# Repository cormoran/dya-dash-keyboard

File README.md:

#  DYA Dash Split Keyboard

## Features

- Controller: XIAO NRF52840
- Firmware: ZMK
- Switch: Kailh Choc v2, hotswappable (2pin)
- AAA battery (1.2V NiMH or 1.5V)
- Touch sensor buttons ([See movie how it works](https://x.com/cormoran707/status/1916127921720463540))
- PMW3610 low power trackball sensor
- LED x 4 x 2 for BLE profile, battery level indication ([See movie how it works](https://youtu.be/y6X2OnoMX-M))
- Hardware capability for below features (Not tested yet)
  - Dual trackball support
  - Wired connection

## Build Guide

- [V2.0 ビルドガイド](./hardware/dya-dash/build-guide/v2/BuildGuide.md)
- [V1.0 (試作) ビルドガイド](./hardware/dya-dash/build-guide/v1/BuildGuide.md)

## Firmware

Firmware is available in https://github.com/cormoran/zmk-keyboard-dya-dash.

You can download pre-built binaries in [the release page](https://github.com/cormoran/zmk-keyboard-dya-dash/releases).

The firmware supports keymapping update with [ZMK studio](https://zmk.studio/).

## Gallery

### Schematic

Left side schematic

### Double trackball supported

### Colors

### Bottom

### LED indicators

4x2 LEDs indicates battery level, connected BLE/USB profiles and active layers depending on the setting.
The schematic and firmware driver is optimized for battery usage. LED modules consume power only when required.

> [!NOTE]
> The picture is old version's one

## Shop

Now on sale in https://cormoran707.booth.pm/

## License

- Firmware (./firmware): MIT. See detail in each git submodule.
- DYA logo  (./img/dya.svg): All rights reserved.
- Other keyboard pictures under ./img: CC BY
- Hardware
  - kicad library (./hardware/kicad_library/\*) and sch (\*.kicad_sch): MIT
  - PCB (\*.kicad_pcb): CC BY-NC
  - Case data (\*.stl): CC BY

完全なコピー品が販売された場合に対応できるように PCB 設計を流用して販売することは禁止していますが、回路設計を真似たり似たような設計のキーボードを作ることを牽制したりする意図はありません。

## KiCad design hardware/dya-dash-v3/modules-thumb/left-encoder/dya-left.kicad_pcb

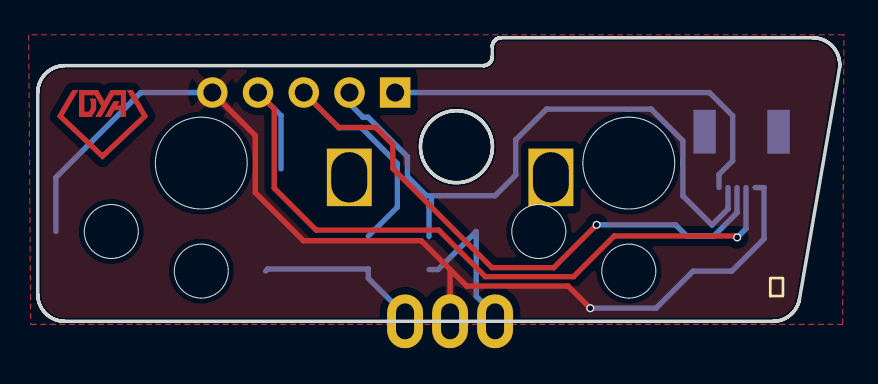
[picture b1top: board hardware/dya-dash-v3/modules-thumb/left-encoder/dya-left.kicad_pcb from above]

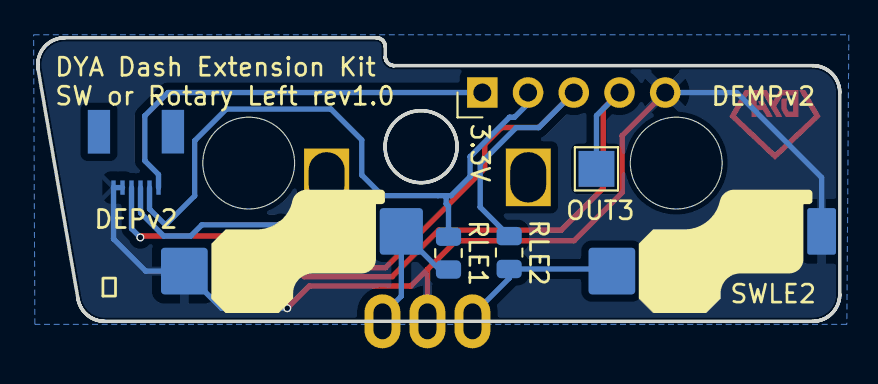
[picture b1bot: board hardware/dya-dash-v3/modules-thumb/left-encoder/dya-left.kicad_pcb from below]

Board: 2 copper layers, 44.6 x 15.8 mm, 8 parts (7 on the bottom side), 7 nets.

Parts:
JLE1: FFC; JUSHUO-AFH34-S06FIA-1H
JLE2: Magnet Connector; PinHeader_1x05_P2.54mm_Vertical
JLE3: Conn_01x01_Socket; TestPoint_Pad_2.0x2.0mm
RLE1, RLE2: 330Ω; R_0805_2012Metric
SWELE1: RotaryEncoder_Switch; RotaryEncoder_EC12E
SWLE1, SWLE2: SW_Push_45deg; Kailh-PG1353-Hotswap-1U

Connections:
3.3V_L: JLE1.1, JLE2.1
ENC1_LE: RLE1.2, SWELE1.B, SWLE1.1
ENC2_LE: RLE2.2, SWELE1.A, SWLE2.2
GNDLE: JLE1.5, JLE1.6, JLE2.5, SWELE1.C, SWLE1.2, SWLE2.1
OUT1: JLE1.2, JLE2.2, RLE1.1
OUT2: JLE1.3, JLE2.3, RLE2.1
OUT3: JLE1.4, JLE2.4, JLE3.1

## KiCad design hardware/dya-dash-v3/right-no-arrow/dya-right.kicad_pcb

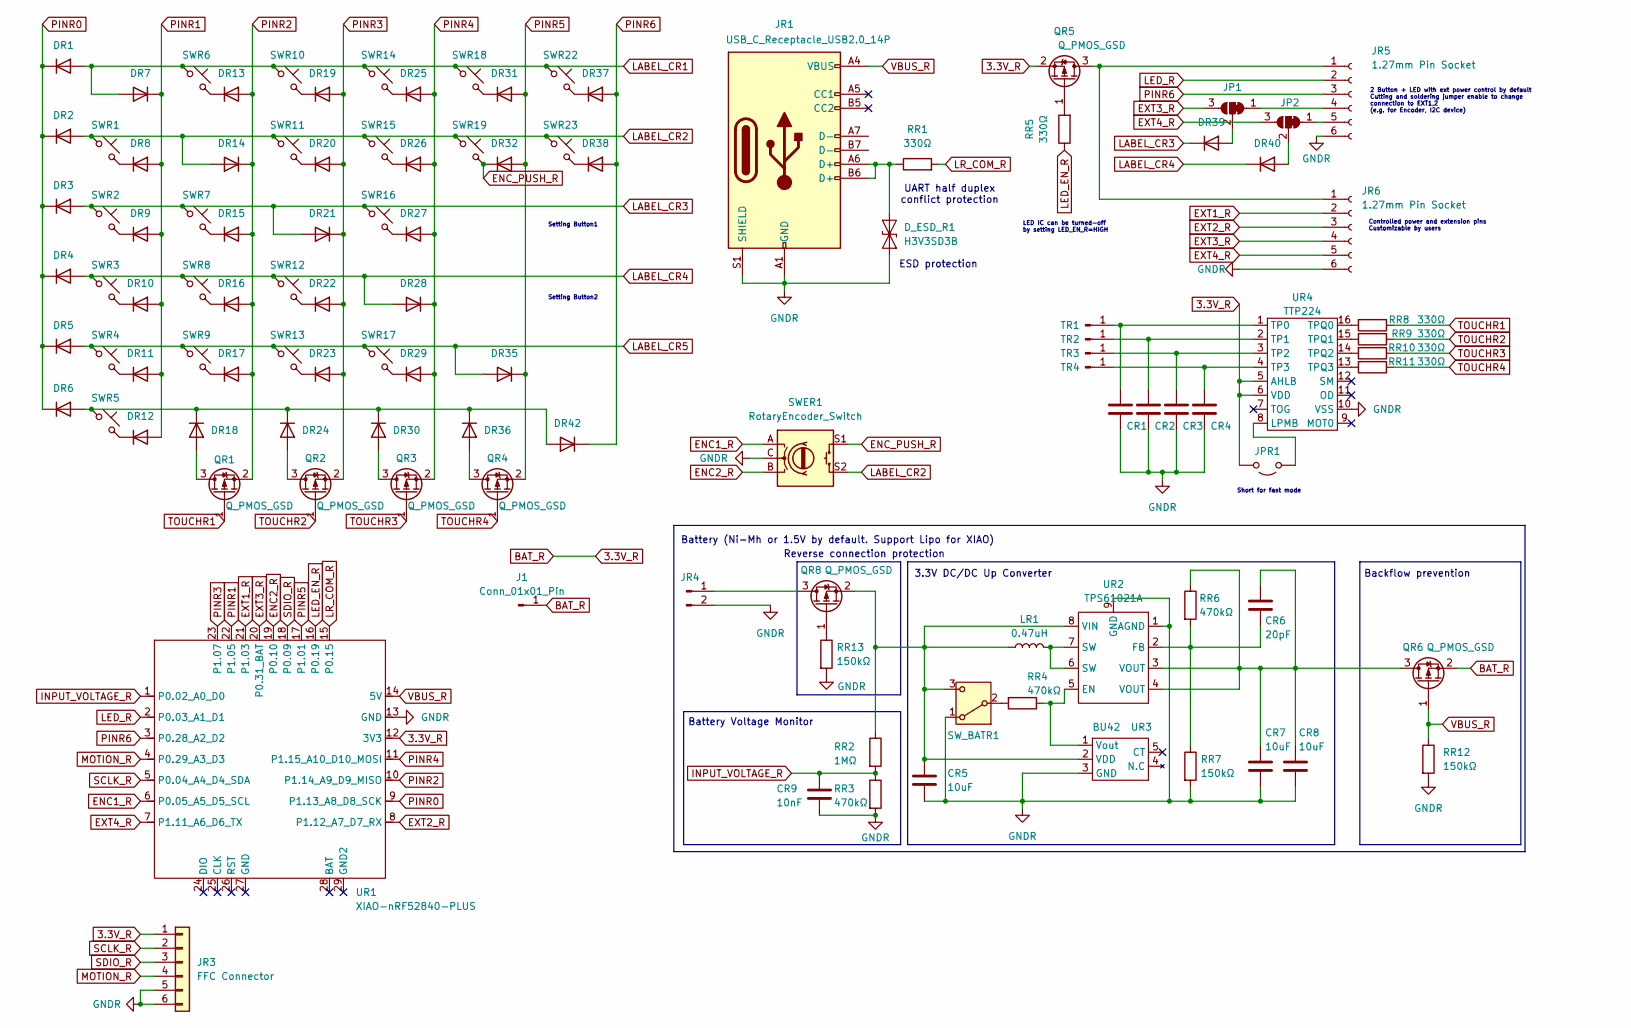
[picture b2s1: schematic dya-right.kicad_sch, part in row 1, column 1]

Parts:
CR1, CR2, CR3, CR4: C_0805_2012Metric
CR5, CR7, CR8: 10uF; C_0805_2012Metric; LCSC C15850
CR6: 20pF; C_0805_2012Metric; LCSC C1798
CR9: 10nF; C_0805_2012Metric
DR1, DR2, DR3, DR4, DR5, DR6, DR7, DR8, DR9, DR10, DR11, DR12, DR13, DR14, DR15, DR16, DR17, DR18, DR19, DR20, DR21, DR22, DR23, DR24, DR25, DR26, DR27, DR28, DR29, DR30, DR31, DR32, DR35, DR36, DR37, DR38, DR39, DR40, DR42: D; D_SOD-123; LCSC C81598
D_ESD_R1: H3V3SD3B; D_SOD-323; LCSC C20615802
J1: Conn_01x01_Pin; TestPoint_Pad_1.5x1.5mm
JP1, JP2: SolderJumper_3_Bridged12; SolderJumper-3_P1.3mm_Bridged12_RoundedPad1.0x1.5mm
JPR1: Jumper_2_Open; SolderJumper-2_P1.3mm_Open_RoundedPad1.0x1.5mm
JR1: USB_C_Receptacle_USB2.0_14P; USB_C_ Recessed_ YTC-TC16-31_1.2mm; LCSC C2927296
JR3: FFC Connector; JUSHUO-AFH34-S06FIA-1H; LCSC C224194
JR4: Conn_01x02_Pin; AAA-battery
JR5, JR6: 1.27mm Pin Socket; PinHeader_1x06_P1.27mm_Vertical
LR1: 0.47uH; L_1008_2520Metric; LCSC C519277
QR1, QR2, QR3, QR4, QR5, QR6: Q_PMOS_GSD; SOT-23; LCSC C15127
QR8: Q_PMOS_GSD; SOT-23; LCSC C144153
RR1, RR5, RR8, RR9, RR10, RR11: 330Ω; R_0805_2012Metric; LCSC C17630
RR2: 1MΩ; R_0805_2012Metric; LCSC C17514
RR3, RR4, RR6: 470kΩ; R_0805_2012Metric; LCSC C17709
RR7, RR12, RR13: 150kΩ; R_0805_2012Metric; LCSC C17470
SWER1: RotaryEncoder_Switch; RotaryEncoder_Alps_EC12E-Switch_Vertical_H20mm
SWR1, SWR2, SWR3, SWR4, SWR5, SWR6, SWR7, SWR8, SWR9, SWR10, SWR11, SWR12, SWR13, SWR14, SWR15, SWR16, SWR17, SWR18, SWR19, SWR22, SWR23: SW_Push_45deg; Kailh-PG1353-Hotswap-1U; LCSC C5333465
SW_BATR1: SW_SPDT; SSSS811101; LCSC C109335
TR1, TR2, TR3, TR4: Conn_01x01_Pin; MountingHole_2.2mm_M2_Pad
UR1: XIAO-nRF52840-PLUS; XIAO_nRF52840_plus
UR2: TPS61021A; WSON-8-1EP_2x2mm_P0.5mm_EP0.9x1.6mm; LCSC C193037
UR3: BU42; BU42XX; LCSC C2066584
UR4: TTP224; SSOP-16_3.9x4.9mm_P0.635mm; LCSC C2890350

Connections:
3.3V_R: J1.1, JPR1.2 (B), JR3.1, QR5.2 (S), QR6.2 (S), UR1.12 (3V3), UR4.5 (AHLB), UR4.6 (VDD)
ENC1_R: SWER1.A, UR1.6 (P0.05_A5_D5_SCL)
ENC2_R: SWER1.B, UR1.19 (P0.10)
ENC_PUSH_R: DR32.1 (K), SWER1.S1, SWR19.2
EXT1_R: JR6.2, UR1.21 (P1.03)
EXT2_R: JR6.3, UR1.8 (P1.12_A7_D7_RX)
EXT3_R: JP1.3 (B), JR6.4, UR1.20 (P0.31_BAT)
EXT4_R: JP2.3 (B), JR6.5, UR1.7 (P1.11_A6_D6_TX)
GNDR: CR1.2, CR2.2, CR3.2, CR4.2, CR5.2, CR7.2, CR8.2, CR9.2, D_ESD_R1.2 (A2), JR1.A1 (GND), JR1.A12 (GND), JR1.B1 (GND), JR1.B12 (GND), JR1.S1 (SHIELD), JR3.5, JR3.6, JR4.2, JR5.6, JR6.6, RR3.2, RR7.2, RR12.2, RR13.2, SWER1.C, SW_BATR1.1 (A), UR1.13 (GND), UR2.1 (AGND), UR2.9 (GND), UR3.3 (GND), UR4.10 (VSS)
INPUT_VOLTAGE_R: CR9.1, RR2.2, RR3.1, UR1.1 (P0.02_A0_D0)
LABEL_CR1: DR1.2 (A), DR7.2 (A), SWR6.1, SWR10.1, SWR14.1, SWR18.1, SWR22.1
LABEL_CR2: DR2.2 (A), DR14.2 (A), SWER1.S2, SWR1.1, SWR11.1, SWR15.1, SWR19.1, SWR23.1
LABEL_CR3: DR3.2 (A), DR21.2 (A), DR39.1 (K), SWR2.1, SWR7.1, SWR16.1
LABEL_CR4: DR4.2 (A), DR28.2 (A), DR40.1 (K), SWR3.1, SWR8.1, SWR12.1
LABEL_CR5: DR5.2 (A), DR35.2 (A), SWR4.1, SWR9.1, SWR13.1, SWR17.1
LED_EN_R: RR5.1, UR1.16 (P0.19)
LED_R: JR5.2, UR1.2 (P0.03_A1_D1)
LR_COM_R: RR1.2, UR1.15 (P0.15)
MOTION_R: JR3.4, UR1.4 (P0.29_A3_D3)
unnamed: DR8.1 (K), SWR1.2
unnamed: DR9.1 (K), SWR2.2
unnamed: DR10.1 (K), SWR3.2
unnamed: DR11.1 (K), SWR4.2
unnamed: DR12.1 (K), SWR5.2
unnamed: DR13.1 (K), SWR6.2
unnamed: DR15.1 (K), SWR7.2
unnamed: DR16.1 (K), SWR8.2
unnamed: DR17.1 (K), SWR9.2
unnamed: DR18.2 (A), QR1.3 (D)
unnamed: DR6.2 (A), DR18.1 (K), DR24.1 (K), DR30.1 (K), DR36.1 (K), DR42.2 (A), SWR5.1
unnamed: DR19.1 (K), SWR10.2
unnamed: DR20.1 (K), SWR11.2
unnamed: DR22.1 (K), SWR12.2
unnamed: DR23.1 (K), SWR13.2
unnamed: DR24.2 (A), QR2.3 (D)
unnamed: DR25.1 (K), SWR14.2
unnamed: DR26.1 (K), SWR15.2
unnamed: DR27.1 (K), SWR16.2
unnamed: DR29.1 (K), SWR17.2
unnamed: DR30.2 (A), QR3.3 (D)
unnamed: DR31.1 (K), SWR18.2
unnamed: DR36.2 (A), QR4.3 (D)
unnamed: DR37.1 (K), SWR22.2
unnamed: DR38.1 (K), SWR23.2
unnamed: DR39.2 (A), JP1.2 (C)
unnamed: DR40.2 (A), JP2.2 (C)
unnamed: D_ESD_R1.1 (A1), JR1.A6 (D+), JR1.B6 (D+), RR1.1
unnamed: JP1.1 (A), JR5.4
unnamed: JP2.1 (A), JR5.5
unnamed: JPR1.1 (A), UR4.8 (LPMB)
unnamed: JR4.1, QR8.3 (D)
unnamed: JR5.1, JR6.1, QR5.3 (D)
unnamed: LR1.2, UR2.6 (SW), UR2.7 (SW)
unnamed: QR5.1 (G), RR5.2
unnamed: CR6.1, CR7.1, CR8.1, QR6.3 (D), RR6.1, UR2.3 (VOUT), UR2.4 (VOUT)
unnamed: QR8.1 (G), RR13.1
unnamed: CR5.1, LR1.1, QR8.2 (S), RR2.1, SW_BATR1.3 (C), UR2.8 (VIN), UR3.2 (VDD)
unnamed: RR4.2, SW_BATR1.2 (B)
unnamed: CR1.1, TR1.1, UR4.1 (TP0)
unnamed: CR2.1, TR2.1, UR4.2 (TP1)
unnamed: CR3.1, TR3.1, UR4.3 (TP2)
unnamed: CR4.1, TR4.1, UR4.4 (TP3)
unnamed: RR4.1, UR2.5 (EN), UR3.1 (Vout)
unnamed: CR6.2, RR6.2, RR7.1, UR2.2 (FB)
unnamed: RR8.2, UR4.16 (TPQ0)
unnamed: RR9.2, UR4.15 (TPQ1)
unnamed: RR10.2, UR4.14 (TPQ2)
unnamed: RR11.2, UR4.13 (TPQ3)
PINR0: DR1.1 (K), DR2.1 (K), DR3.1 (K), DR4.1 (K), DR5.1 (K), DR6.1 (K), UR1.9 (P1.13_A8_D8_SCK)
PINR1: DR7.1 (K), DR8.2 (A), DR9.2 (A), DR10.2 (A), DR11.2 (A), DR12.2 (A), UR1.22 (P1.05)
PINR2: DR13.2 (A), DR14.1 (K), DR15.2 (A), DR16.2 (A), DR17.2 (A), QR1.2 (S), UR1.10 (P1.14_A9_D9_MISO)
PINR3: DR19.2 (A), DR20.2 (A), DR21.1 (K), DR22.2 (A), DR23.2 (A), QR2.2 (S), UR1.23 (P1.07)
PINR4: DR25.2 (A), DR26.2 (A), DR27.2 (A), DR28.1 (K), DR29.2 (A), QR3.2 (S), UR1.11 (P1.15_A10_D10_MOSI)
PINR5: DR31.2 (A), DR32.2 (A), DR35.1 (K), QR4.2 (S), UR1.17 (P1.01)
PINR6: DR37.2 (A), DR38.2 (A), DR42.1 (K), JR5.3, UR1.3 (P0.28_A2_D2)
SCLK_R: JR3.2, UR1.5 (P0.04_A4_D4_SDA)
SDIO_R: JR3.3, UR1.18 (P0.09)
TOUCHR1: QR1.1 (G), RR8.1
TOUCHR2: QR2.1 (G), RR9.1
TOUCHR3: QR3.1 (G), RR10.1
TOUCHR4: QR4.1 (G), RR11.1
VBUS_R: JR1.A4 (VBUS), JR1.A9 (VBUS), JR1.B4 (VBUS), JR1.B9 (VBUS), QR6.1 (G), RR12.1, UR1.14 (5V)

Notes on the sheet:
Battery (Ni-Mh or 1.5V by default. Support Lipo for XIAO)
2 Button + LED with ext power control by default Cutting and soldering jumper enable to change connection to EXT1,2 (e.g. for Encoder, I2C device)
Short for fast mode
Setting Button1
3.3V DC/DC Up Converter
ESD protection
UART half duplex conflict protection
Backflow prevention
Reverse connection protection
LED IC can be turned-off by setting LED_EN_R=HIGH
Battery Voltage Monitor
Setting Button2
Controlled power and extension pins Customizable by users

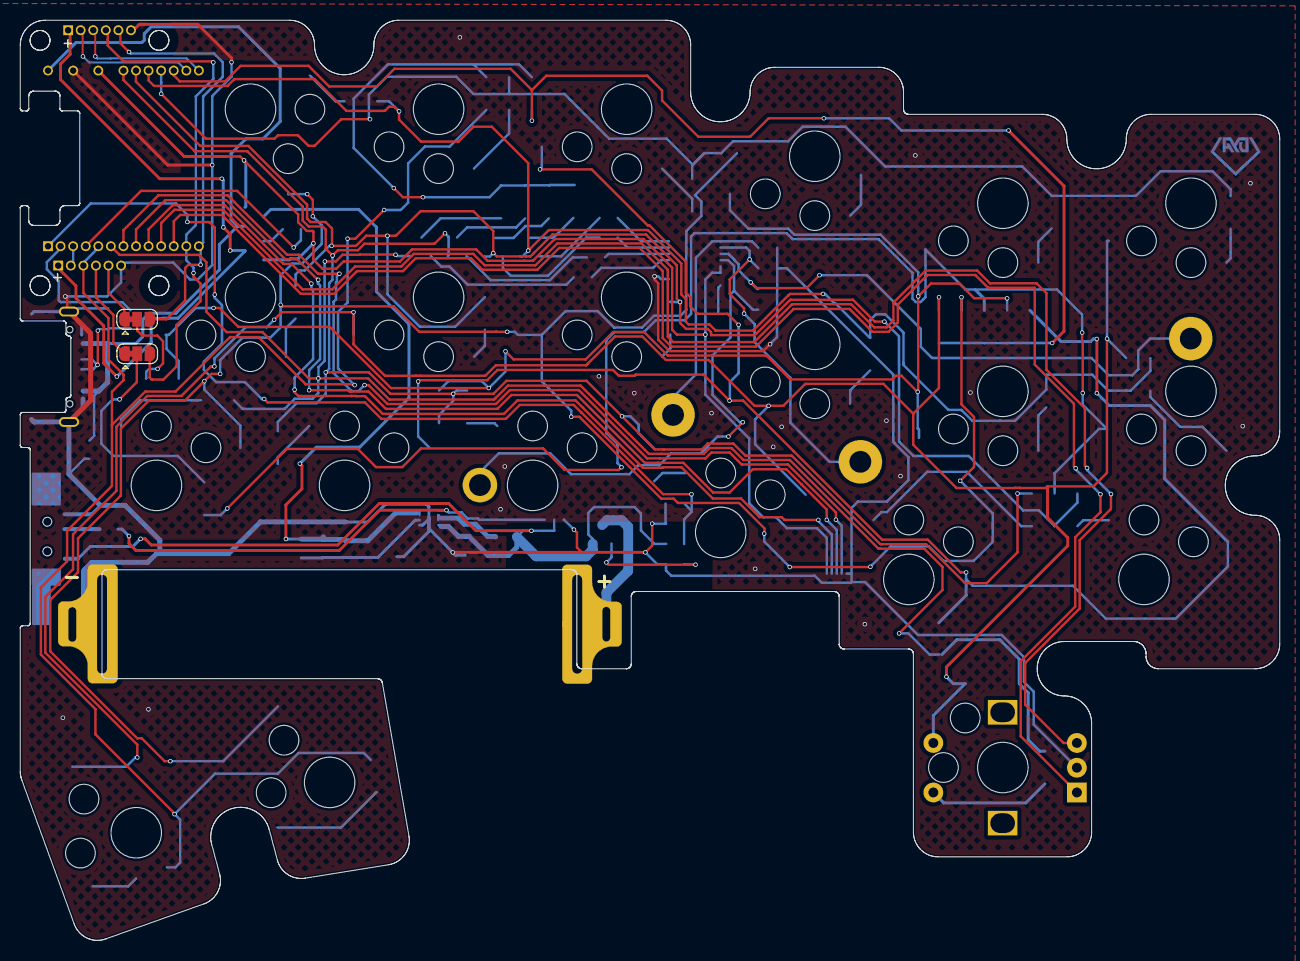
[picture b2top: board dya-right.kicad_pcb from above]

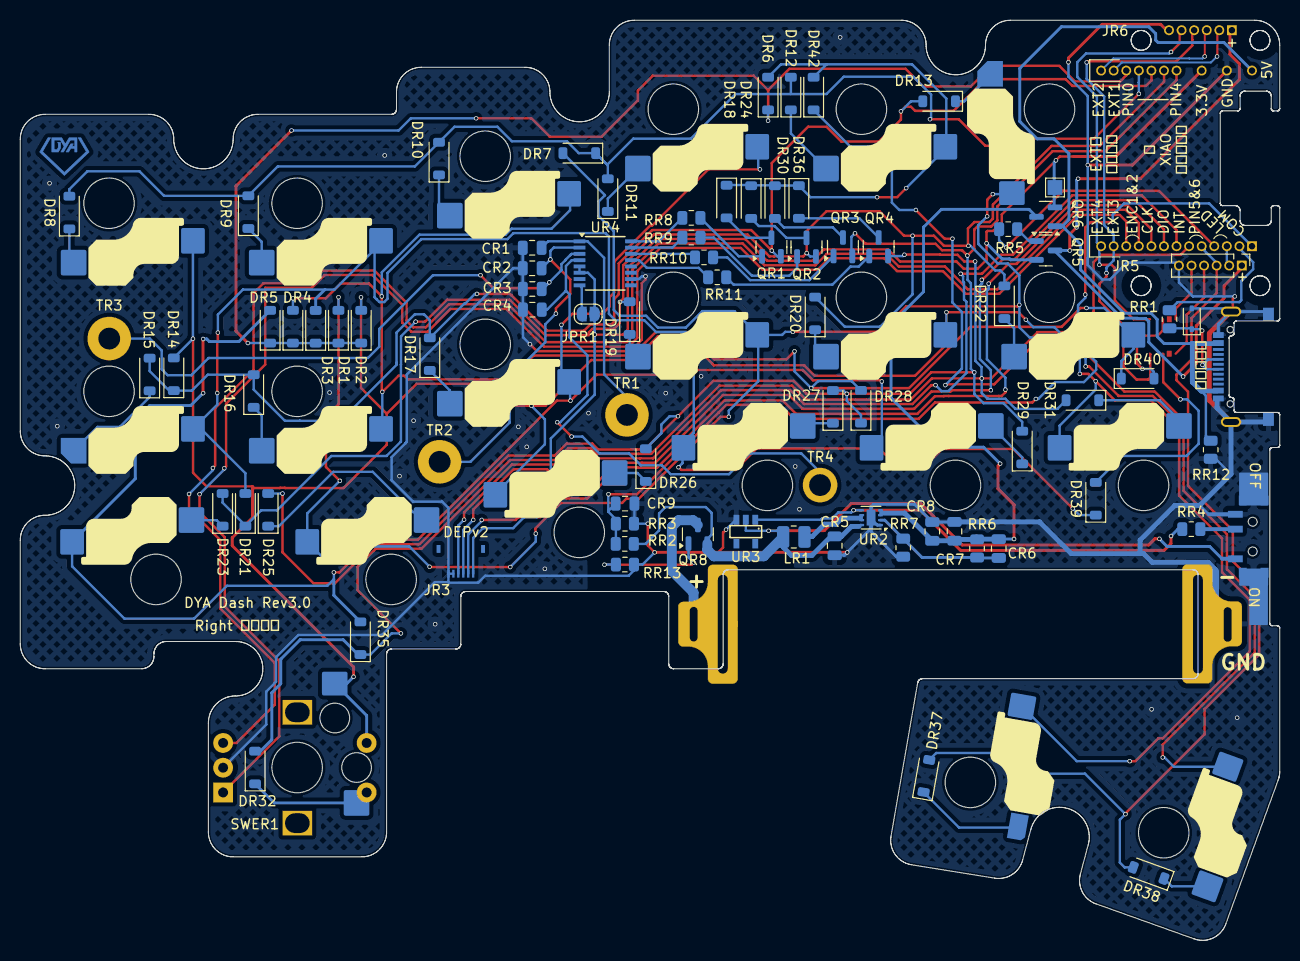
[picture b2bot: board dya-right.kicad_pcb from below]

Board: 2 copper layers, 127.2 x 92.9 mm, 110 parts (104 on the bottom side), 82 nets.

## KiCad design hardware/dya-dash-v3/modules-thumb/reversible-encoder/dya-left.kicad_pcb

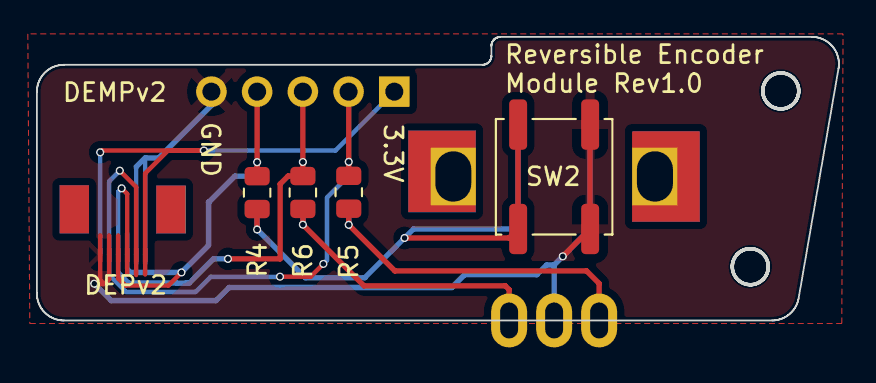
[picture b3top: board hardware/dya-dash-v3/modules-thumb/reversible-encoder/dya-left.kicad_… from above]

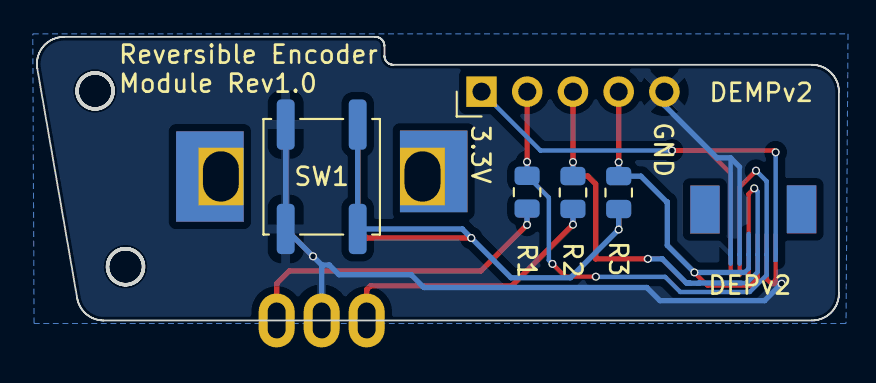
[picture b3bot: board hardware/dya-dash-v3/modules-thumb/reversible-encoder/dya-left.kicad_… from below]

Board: 2 copper layers, 44.6 x 15.8 mm, 12 parts (6 on the bottom side), 8 nets.

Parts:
J1, J3: FFC; JUSHUO-AFH34-S06FIA-1H
J2: Magnet Connector; PinHeader_1x05_P2.54mm_Vertical
R1, R2, R3, R4, R5, R6: 330Ω; R_0805_2012Metric
SW1, SW2: SW_Push_45deg; SW_Push_1P1T_NO_CK_KSC6xxJ
SWE1: RotaryEncoder_Switch; RotaryEncoder_EC12E

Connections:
3.3V_L: J1.1, J2.1, J3.1
ENC1_LE: R1.2, R5.2, SWE1.B
ENC2_LE: R2.2, R6.2, SWE1.A
GNDLE: J1.5, J1.6, J2.5, J3.5, J3.6, SW1.2, SW2.1, SWE1.C
unnamed: R3.1, R4.1, SW1.1, SW2.2
OUT1: J1.2, J2.2, J3.2, R1.1, R5.1
OUT2: J1.3, J2.3, J3.3, R2.1, R6.1
OUT3: J1.4, J2.4, J3.4, R3.2, R4.2

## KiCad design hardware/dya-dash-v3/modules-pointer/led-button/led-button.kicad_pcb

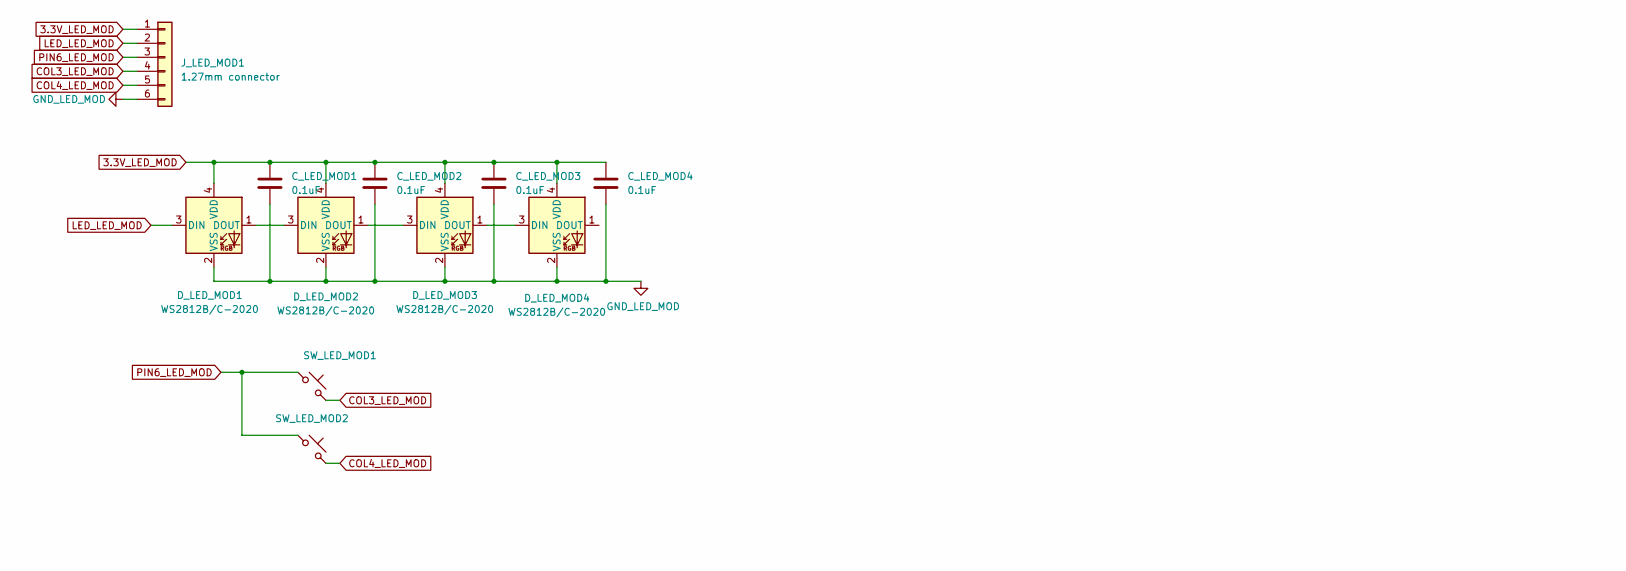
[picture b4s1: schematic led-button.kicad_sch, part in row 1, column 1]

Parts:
C_LED_MOD1, C_LED_MOD2, C_LED_MOD3, C_LED_MOD4: 0.1uF; C_0402_1005Metric; LCSC C1525
D_LED_MOD1, D_LED_MOD2, D_LED_MOD3, D_LED_MOD4: WS2812B/C-2020; LED_WS2812B-2020_PLCC4_2.0x2.0mm; LCSC C2976072
J_LED_MOD1: 1.27mm connector; PinHeader_1x06_P1.27mm_Vertical
SW_LED_MOD1, SW_LED_MOD2: SW_Push; SW_PUSH_1P1T_6x3.5mm_H4.3_APEM_MJTP1243

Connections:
3.3V_LED_MOD: C_LED_MOD1.1, C_LED_MOD2.1, C_LED_MOD3.1, C_LED_MOD4.1, D_LED_MOD1.4 (VDD), D_LED_MOD2.4 (VDD), D_LED_MOD3.4 (VDD), D_LED_MOD4.4 (VDD), J_LED_MOD1.1
COL3_LED_MOD: J_LED_MOD1.4, SW_LED_MOD1.2
COL4_LED_MOD: J_LED_MOD1.5, SW_LED_MOD2.2
GND_LED_MOD: C_LED_MOD1.2, C_LED_MOD2.2, C_LED_MOD3.2, C_LED_MOD4.2, D_LED_MOD1.2 (VSS), D_LED_MOD2.2 (VSS), D_LED_MOD3.2 (VSS), D_LED_MOD4.2 (VSS), J_LED_MOD1.6
LED_LED_MOD: D_LED_MOD1.3 (DIN), J_LED_MOD1.2
unnamed: D_LED_MOD1.1 (DOUT), D_LED_MOD2.3 (DIN)
unnamed: D_LED_MOD2.1 (DOUT), D_LED_MOD3.3 (DIN)
unnamed: D_LED_MOD3.1 (DOUT), D_LED_MOD4.3 (DIN)
PIN6_LED_MOD: J_LED_MOD1.3, SW_LED_MOD1.1, SW_LED_MOD2.1

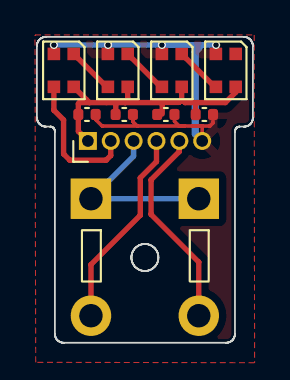
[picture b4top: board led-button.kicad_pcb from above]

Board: 2 copper layers, 12.0 x 17.0 mm, 11 parts (0 on the bottom side), 9 nets.

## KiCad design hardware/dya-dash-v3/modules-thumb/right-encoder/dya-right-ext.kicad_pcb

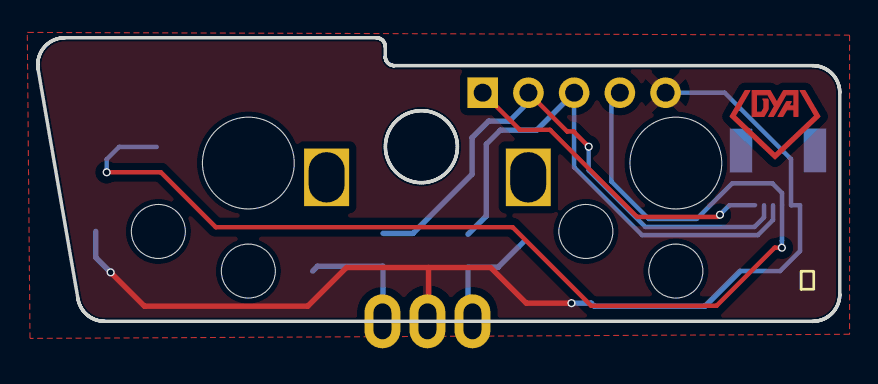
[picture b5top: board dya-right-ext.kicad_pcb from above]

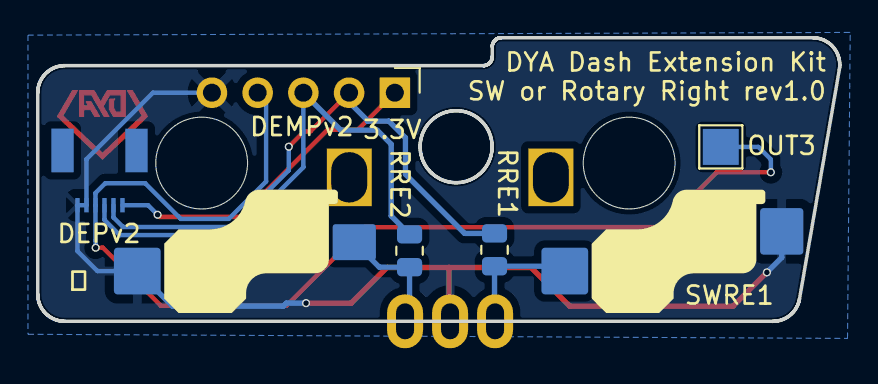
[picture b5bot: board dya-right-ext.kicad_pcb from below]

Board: 2 copper layers, 44.6 x 15.8 mm, 8 parts (7 on the bottom side), 7 nets.

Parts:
JRE1: FFC; JUSHUO-AFH34-S06FIA-1H
JRE2: Magnet Connector; PinHeader_1x05_P2.54mm_Vertical
JRE3: Conn_01x01_Socket; TestPoint_Pad_2.0x2.0mm
RRE1, RRE2: 330Ω; R_0805_2012Metric
SWERE1: RotaryEncoder_Switch; RotaryEncoder_EC12E
SWRE1, SWRE2: SW_Push_45deg; Kailh-PG1353-Hotswap-1U

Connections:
3.3V_RE: JRE1.1, JRE2.1
ENC1_RE: RRE1.2, SWERE1.A, SWRE1.2
ENC2_RE: RRE2.2, SWERE1.B, SWRE2.1
GNDRE: JRE1.5, JRE1.6, JRE2.5, SWERE1.C, SWRE1.1, SWRE2.2
OUT_RE1: JRE1.2, JRE2.2, RRE1.1
OUT_RE2: JRE1.3, JRE2.3, RRE2.1
OUT_RE3: JRE1.4, JRE2.4, JRE3.1

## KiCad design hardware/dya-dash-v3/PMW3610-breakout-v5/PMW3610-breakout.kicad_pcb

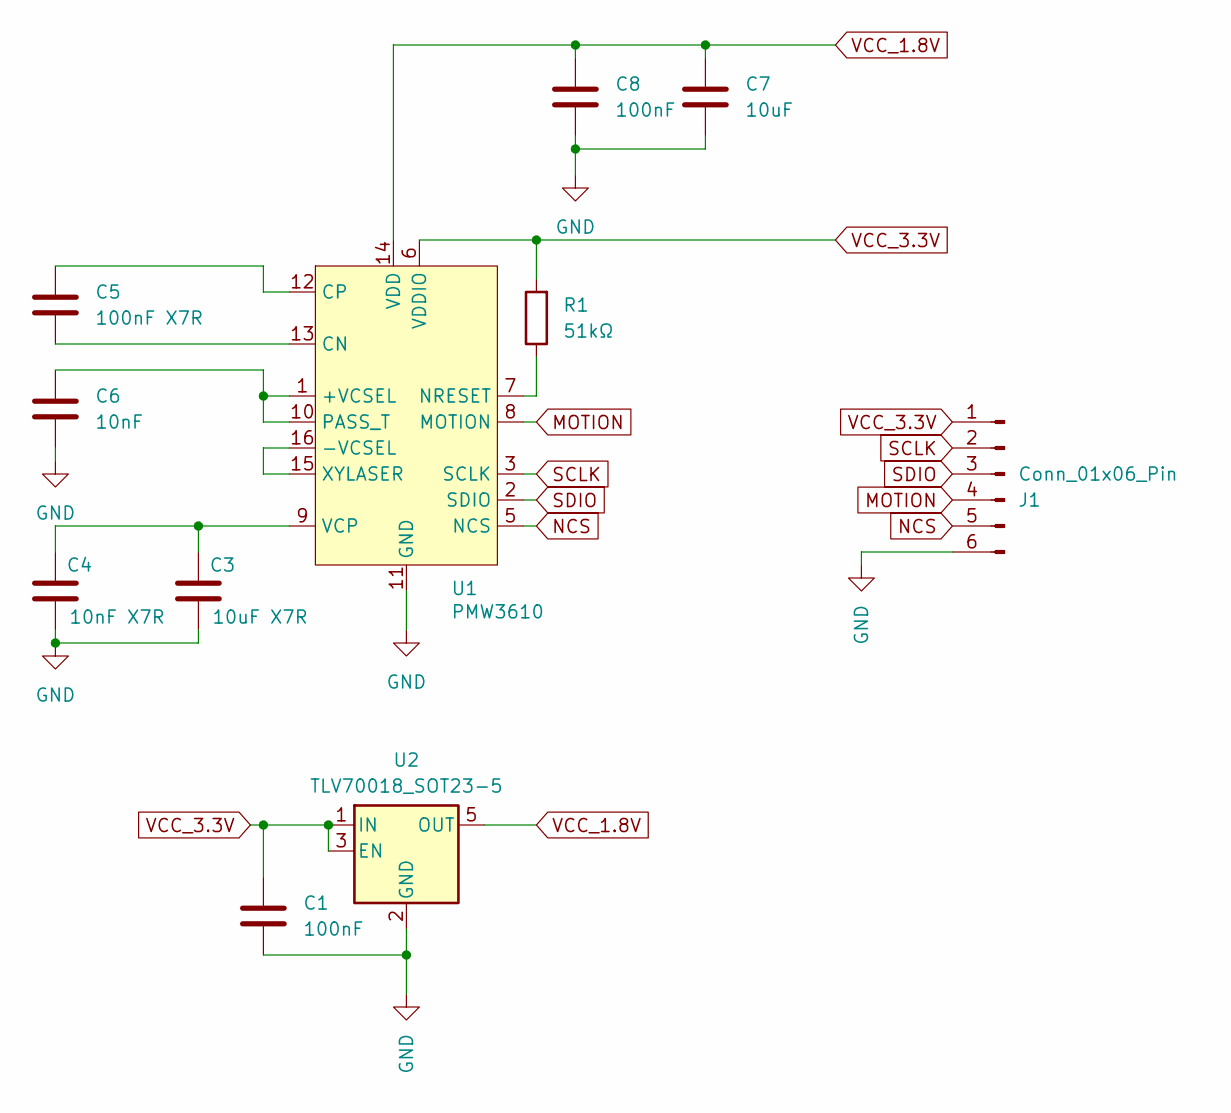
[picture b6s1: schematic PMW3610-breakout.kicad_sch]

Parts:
C1, C8: 100nF; C_0402_1005Metric; LCSC C1525
C3: 10uF X7R; C_0402_1005Metric; LCSC C15525
C4: 10nF X7R; C_0402_1005Metric; LCSC C15195
C5: 100nF X7R; C_0402_1005Metric; LCSC C1525
C6: 10nF; C_0402_1005Metric; LCSC C15195
C7: 10uF; C_0402_1005Metric; LCSC C15525
J1: Conn_01x06_Pin; JUSHUO-AFH34-S06FIA-1H; LCSC C224194
R1: 51kΩ; R_0402_1005Metric; LCSC C25794
U1: PMW3610; PMW3610DM-SUDU 16Pin
U2: TLV70018_SOT23-5; SOT-23-5; LCSC C79924

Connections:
GND: C1.2, C3.2, C4.2, C6.2, C7.2, C8.2, J1.6, U1.11 (GND), U2.2 (GND)
MOTION: J1.4, U1.8 (MOTION)
NCS: J1.5, U1.5 (NCS)
unnamed: C6.1, U1.1 (+VCSEL), U1.10 (PASS_T)
unnamed: U1.15 (XYLASER), U1.16 (-VCSEL)
unnamed: C5.2, U1.13 (CN)
unnamed: C5.1, U1.12 (CP)
unnamed: R1.1, U1.7 (NRESET)
unnamed: C3.1, C4.1, U1.9 (VCP)
SCLK: J1.2, U1.3 (SCLK)
SDIO: J1.3, U1.2 (SDIO)
VCC_1.8V: C7.1, C8.1, U1.14 (VDD), U2.5 (OUT)
VCC_3.3V: C1.1, J1.1, R1.2, U1.6 (VDDIO), U2.1 (IN), U2.3 (EN)

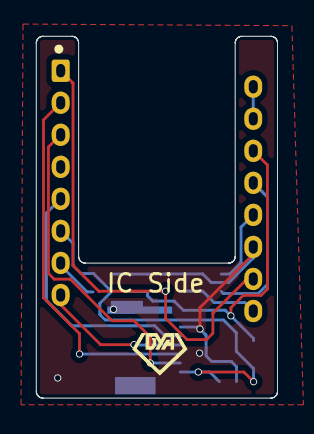
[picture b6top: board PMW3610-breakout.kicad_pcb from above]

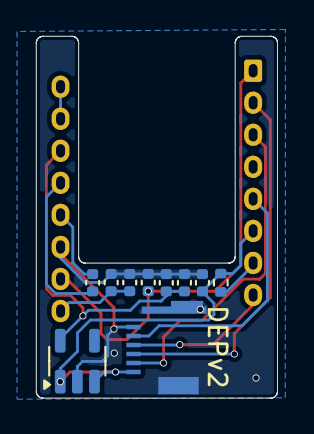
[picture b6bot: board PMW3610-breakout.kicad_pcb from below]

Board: 2 copper layers, 13.4 x 20.1 mm, 11 parts (10 on the bottom side), 13 nets.

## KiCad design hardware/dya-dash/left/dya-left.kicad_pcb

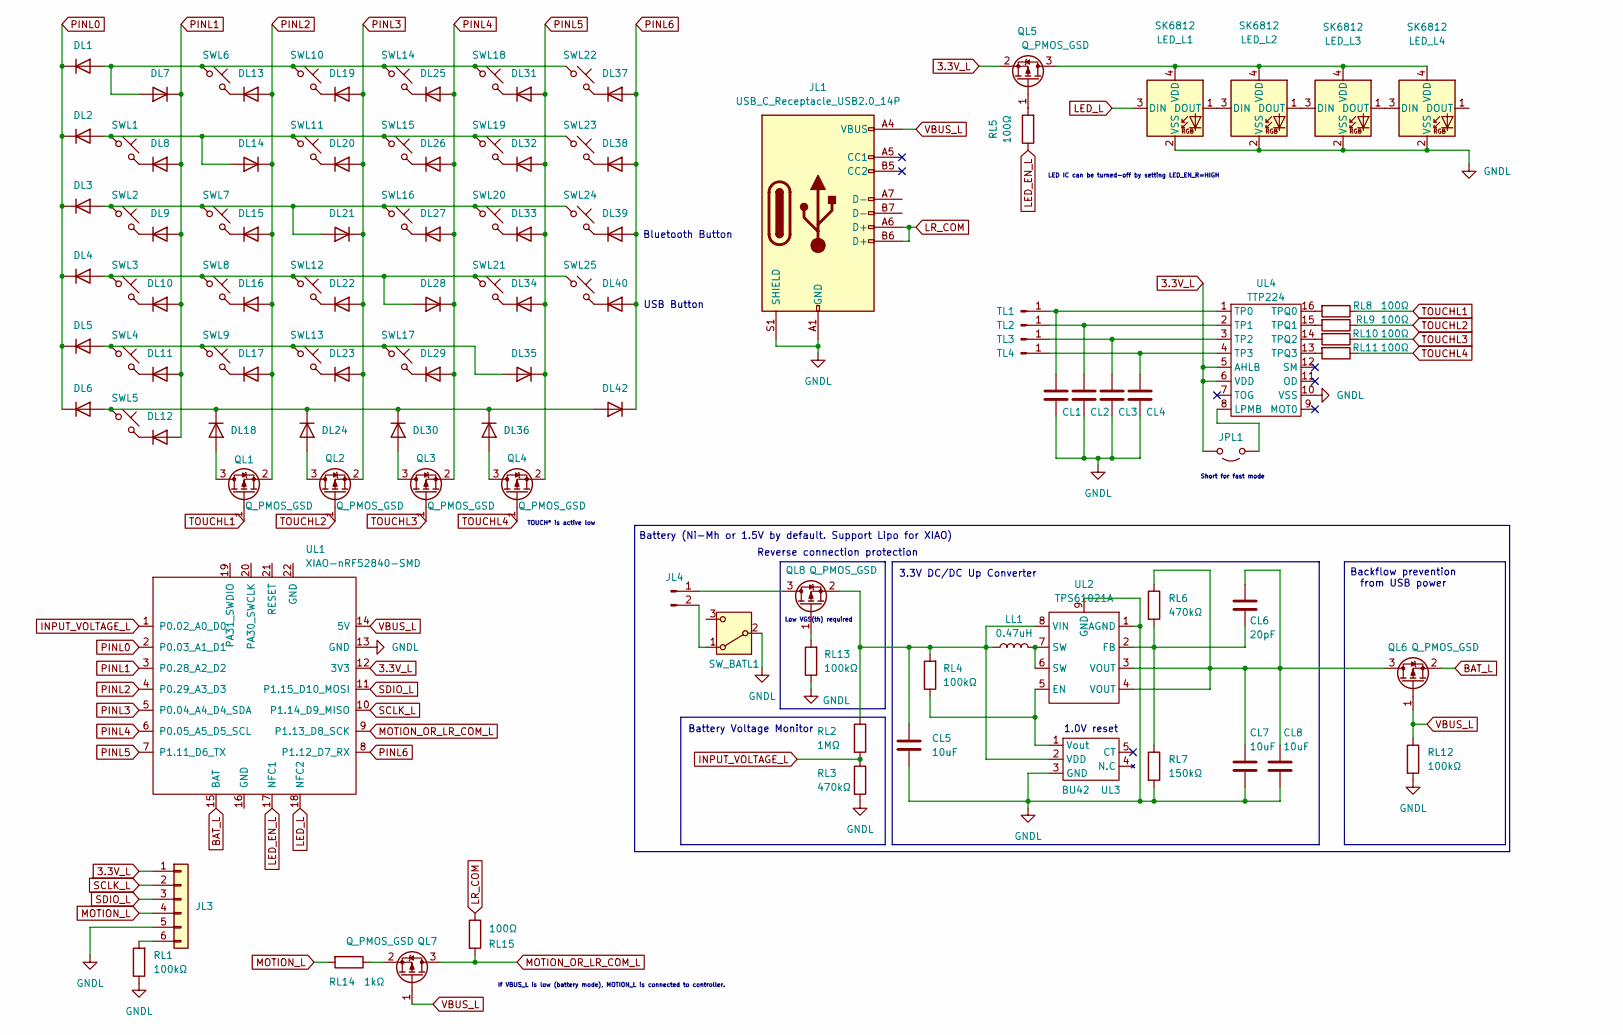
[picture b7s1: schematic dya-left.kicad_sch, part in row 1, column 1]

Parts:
CL1, CL2, CL3, CL4: C_0805_2012Metric
CL5, CL7, CL8: 10uF; C_0805_2012Metric; LCSC C15850
CL6: 20pF; C_0805_2012Metric; LCSC C1798
DL1, DL2, DL3, DL4, DL5, DL6, DL7, DL8, DL9, DL10, DL11, DL12, DL13, DL14, DL15, DL16, DL17, DL18, DL19, DL20, DL21, DL22, DL23, DL24, DL25, DL26, DL27, DL28, DL29, DL30, DL31, DL32, DL33, DL34, DL35, DL36, DL37, DL38, DL39, DL40, DL42: D; D_SOD-123; LCSC C81598
JL1: USB_C_Receptacle_USB2.0_14P; USB_C_Receptacle_G-Switch_GT-USB-7010ASV; LCSC C2927038
JL3: Conn_01x04; JUSHUO-AFH34-S06FIA-1H; LCSC C5139821
JL4: Conn_01x02_Pin; AAA-battery
JPL1: Jumper_2_Open; SolderJumper-2_P1.3mm_Open_RoundedPad1.0x1.5mm
LED_L1, LED_L2, LED_L3, LED_L4: SK6812; LED_SK6812MINI-E_BL; LCSC C5149201
LL1: 0.47uH; L_1008_2520Metric; LCSC C519277
QL1, QL2, QL3, QL4, QL5, QL6, QL7: Q_PMOS_GSD; SOT-23; LCSC C15127
QL8: Q_PMOS_GSD; SOT-23; LCSC C144153
RL1, RL4, RL12, RL13: 100kΩ; R_0805_2012Metric; LCSC C149504
RL2: 1MΩ; R_0805_2012Metric; LCSC C17514
RL3, RL6: 470kΩ; R_0805_2012Metric; LCSC C17709
RL5, RL8, RL9, RL10, RL11, RL15: 100Ω; R_0805_2012Metric; LCSC C17408
RL7: 150kΩ; R_0805_2012Metric; LCSC C17470
RL14: 1kΩ; R_0805_2012Metric; LCSC C17513
SWL1, SWL2, SWL3, SWL4, SWL5, SWL6, SWL7, SWL8, SWL9, SWL10, SWL11, SWL12, SWL13, SWL14, SWL15, SWL16, SWL17, SWL18, SWL19, SWL20, SWL21, SWL22, SWL23: SW_Push_45deg; Kailh-PG1353-Hotswap-1U; LCSC C5333465
SWL24, SWL25: SW_Push_45deg; Push_PTS636SM43SMTR
SW_BATL1: SW_SPDT; MK-12C02-G015; LCSC C2890358
TL1, TL2: Conn_01x01_Pin; MountingHole_2.2mm_M2_Pad
TL3, TL4: Conn_01x01_Pin; SolderWirePad_1x01_SMD_1x2mm
UL1: XIAO-nRF52840-SMD
UL2: TPS61021A; WSON-8-1EP_2x2mm_P0.5mm_EP0.9x1.6mm; LCSC C193037
UL3: BU42; BU42XX; LCSC C2066584
UL4: TTP224; SSOP-16_3.9x4.9mm_P0.635mm; LCSC C2890350

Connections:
3.3V_L: JL3.1, JPL1.2 (B), QL5.2 (S), UL1.12 (3V3), UL4.5 (AHLB), UL4.6 (VDD)
BAT_L: QL6.2 (S), UL1.15 (BAT)
GNDL: CL1.2, CL2.2, CL3.2, CL4.2, CL5.2, CL7.2, CL8.2, JL1.A1 (GND), JL1.A12 (GND), JL1.B1 (GND), JL1.B12 (GND), JL1.S1 (SHIELD), JL3.5, LED_L1.2 (VSS), LED_L2.2 (VSS), LED_L3.2 (VSS), LED_L4.2 (VSS), RL1.1, RL3.2, RL7.2, RL12.2, RL13.1, SW_BATL1.2 (B), UL1.13 (GND), UL2.1 (AGND), UL2.9 (GND), UL3.3 (GND), UL4.10 (VSS)
INPUT_VOLTAGE_L: RL2.2, RL3.1, UL1.1 (P0.02_A0_D0)
LED_EN_L: RL5.1, UL1.17 (NFC1)
LED_L: LED_L1.3 (DIN), UL1.18 (NFC2)
LR_COM: JL1.A6 (D+), JL1.B6 (D+), RL15.1
MOTION_L: JL3.4, RL14.2
MOTION_OR_LR_COM_L: QL7.3 (D), RL15.2, UL1.9 (P1.13_D8_SCK)
unnamed: DL1.2 (A), DL7.2 (A), SWL6.1, SWL10.1, SWL14.1, SWL18.1, SWL22.1
unnamed: DL8.1 (K), SWL1.2
unnamed: DL9.1 (K), SWL2.2
unnamed: DL10.1 (K), SWL3.2
unnamed: DL11.1 (K), SWL4.2
unnamed: DL12.1 (K), SWL5.2
unnamed: DL13.1 (K), SWL6.2
unnamed: DL2.2 (A), DL14.2 (A), SWL1.1, SWL11.1, SWL15.1, SWL19.1, SWL23.1
unnamed: DL15.1 (K), SWL7.2
unnamed: DL16.1 (K), SWL8.2
unnamed: DL17.1 (K), SWL9.2
unnamed: DL18.2 (A), QL1.3 (D)
unnamed: DL6.2 (A), DL18.1 (K), DL24.1 (K), DL30.1 (K), DL36.1 (K), DL42.2 (A), SWL5.1
unnamed: DL19.1 (K), SWL10.2
unnamed: DL20.1 (K), SWL11.2
unnamed: DL3.2 (A), DL21.2 (A), SWL2.1, SWL7.1, SWL16.1, SWL20.1, SWL24.1
unnamed: DL22.1 (K), SWL12.2
unnamed: DL23.1 (K), SWL13.2
unnamed: DL24.2 (A), QL2.3 (D)
unnamed: DL25.1 (K), SWL14.2
unnamed: DL26.1 (K), SWL15.2
unnamed: DL27.1 (K), SWL16.2
unnamed: DL4.2 (A), DL28.2 (A), SWL3.1, SWL8.1, SWL12.1, SWL21.1, SWL25.1
unnamed: DL29.1 (K), SWL17.2
unnamed: DL30.2 (A), QL3.3 (D)
unnamed: DL31.1 (K), SWL18.2
unnamed: DL32.1 (K), SWL19.2
unnamed: DL33.1 (K), SWL20.2
unnamed: DL34.1 (K), SWL21.2
unnamed: DL5.2 (A), DL35.2 (A), SWL4.1, SWL9.1, SWL13.1, SWL17.1
unnamed: DL36.2 (A), QL4.3 (D)
unnamed: DL37.1 (K), SWL22.2
unnamed: DL38.1 (K), SWL23.2
unnamed: DL39.1 (K), SWL24.2
unnamed: DL40.1 (K), SWL25.2
unnamed: JL3.6, RL1.2
unnamed: JL4.1, QL8.3 (D)
unnamed: JL4.2, SW_BATL1.1 (A)
unnamed: JPL1.1 (A), UL4.8 (LPMB)
unnamed: LED_L1.1 (DOUT), LED_L2.3 (DIN)
unnamed: LED_L1.4 (VDD), LED_L2.4 (VDD), LED_L3.4 (VDD), LED_L4.4 (VDD), QL5.3 (D)
unnamed: LED_L2.1 (DOUT), LED_L3.3 (DIN)
unnamed: LED_L3.1 (DOUT), LED_L4.3 (DIN)
unnamed: LL1.2, UL2.6 (SW), UL2.7 (SW)
unnamed: QL5.1 (G), RL5.2
unnamed: CL6.1, CL7.1, CL8.1, QL6.3 (D), RL6.1, UL2.3 (VOUT), UL2.4 (VOUT)
unnamed: QL7.2 (S), RL14.1
unnamed: QL8.1 (G), RL13.2
unnamed: CL5.1, LL1.1, QL8.2 (S), RL2.1, RL4.2, UL2.8 (VIN), UL3.2 (VDD)
unnamed: CL1.1, TL1.1, UL4.1 (TP0)
unnamed: CL2.1, TL2.1, UL4.2 (TP1)
unnamed: CL3.1, TL3.1, UL4.3 (TP2)
unnamed: CL4.1, TL4.1, UL4.4 (TP3)
unnamed: RL4.1, UL2.5 (EN), UL3.1 (Vout)
unnamed: CL6.2, RL6.2, RL7.1, UL2.2 (FB)
unnamed: RL8.2, UL4.16 (TPQ0)
unnamed: RL9.2, UL4.15 (TPQ1)
unnamed: RL10.2, UL4.14 (TPQ2)
unnamed: RL11.2, UL4.13 (TPQ3)
PINL0: DL1.1 (K), DL2.1 (K), DL3.1 (K), DL4.1 (K), DL5.1 (K), DL6.1 (K), UL1.2 (P0.03_A1_D1)
PINL1: DL7.1 (K), DL8.2 (A), DL9.2 (A), DL10.2 (A), DL11.2 (A), DL12.2 (A), UL1.3 (P0.28_A2_D2)
PINL2: DL13.2 (A), DL14.1 (K), DL15.2 (A), DL16.2 (A), DL17.2 (A), QL1.2 (S), UL1.4 (P0.29_A3_D3)
PINL3: DL19.2 (A), DL20.2 (A), DL21.1 (K), DL22.2 (A), DL23.2 (A), QL2.2 (S), UL1.5 (P0.04_A4_D4_SDA)
PINL4: DL25.2 (A), DL26.2 (A), DL27.2 (A), DL28.1 (K), DL29.2 (A), QL3.2 (S), UL1.6 (P0.05_A5_D5_SCL)
PINL5: DL31.2 (A), DL32.2 (A), DL33.2 (A), DL34.2 (A), DL35.1 (K), QL4.2 (S), UL1.7 (P1.11_D6_TX)
PINL6: DL37.2 (A), DL38.2 (A), DL39.2 (A), DL40.2 (A), DL42.1 (K), UL1.8 (P1.12_D7_RX)
SCLK_L: JL3.2, UL1.10 (P1.14_D9_MISO)
SDIO_L: JL3.3, UL1.11 (P1.15_D10_MOSI)
TOUCHL1: QL1.1 (G), RL8.1
TOUCHL2: QL2.1 (G), RL9.1
TOUCHL3: QL3.1 (G), RL10.1
TOUCHL4: QL4.1 (G), RL11.1
VBUS_L: JL1.A4 (VBUS), JL1.A9 (VBUS), JL1.B4 (VBUS), JL1.B9 (VBUS), QL6.1 (G), QL7.1 (G), RL12.1, UL1.14 (5V)

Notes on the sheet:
If VBUS_L is low (battery mode), MOTION_L is connected to controller.
Low VGS(th) required
Battery (Ni-Mh or 1.5V by default. Support Lipo for XIAO)
USB Button
1.0V reset
Bluetooth Button
Short for fast mode
TOUCH* is active low
Reverse connection protection
3.3V DC/DC Up Converter
Backflow prevention from USB power
LED IC can be turned-off by setting LED_EN_R=HIGH
Battery Voltage Monitor
